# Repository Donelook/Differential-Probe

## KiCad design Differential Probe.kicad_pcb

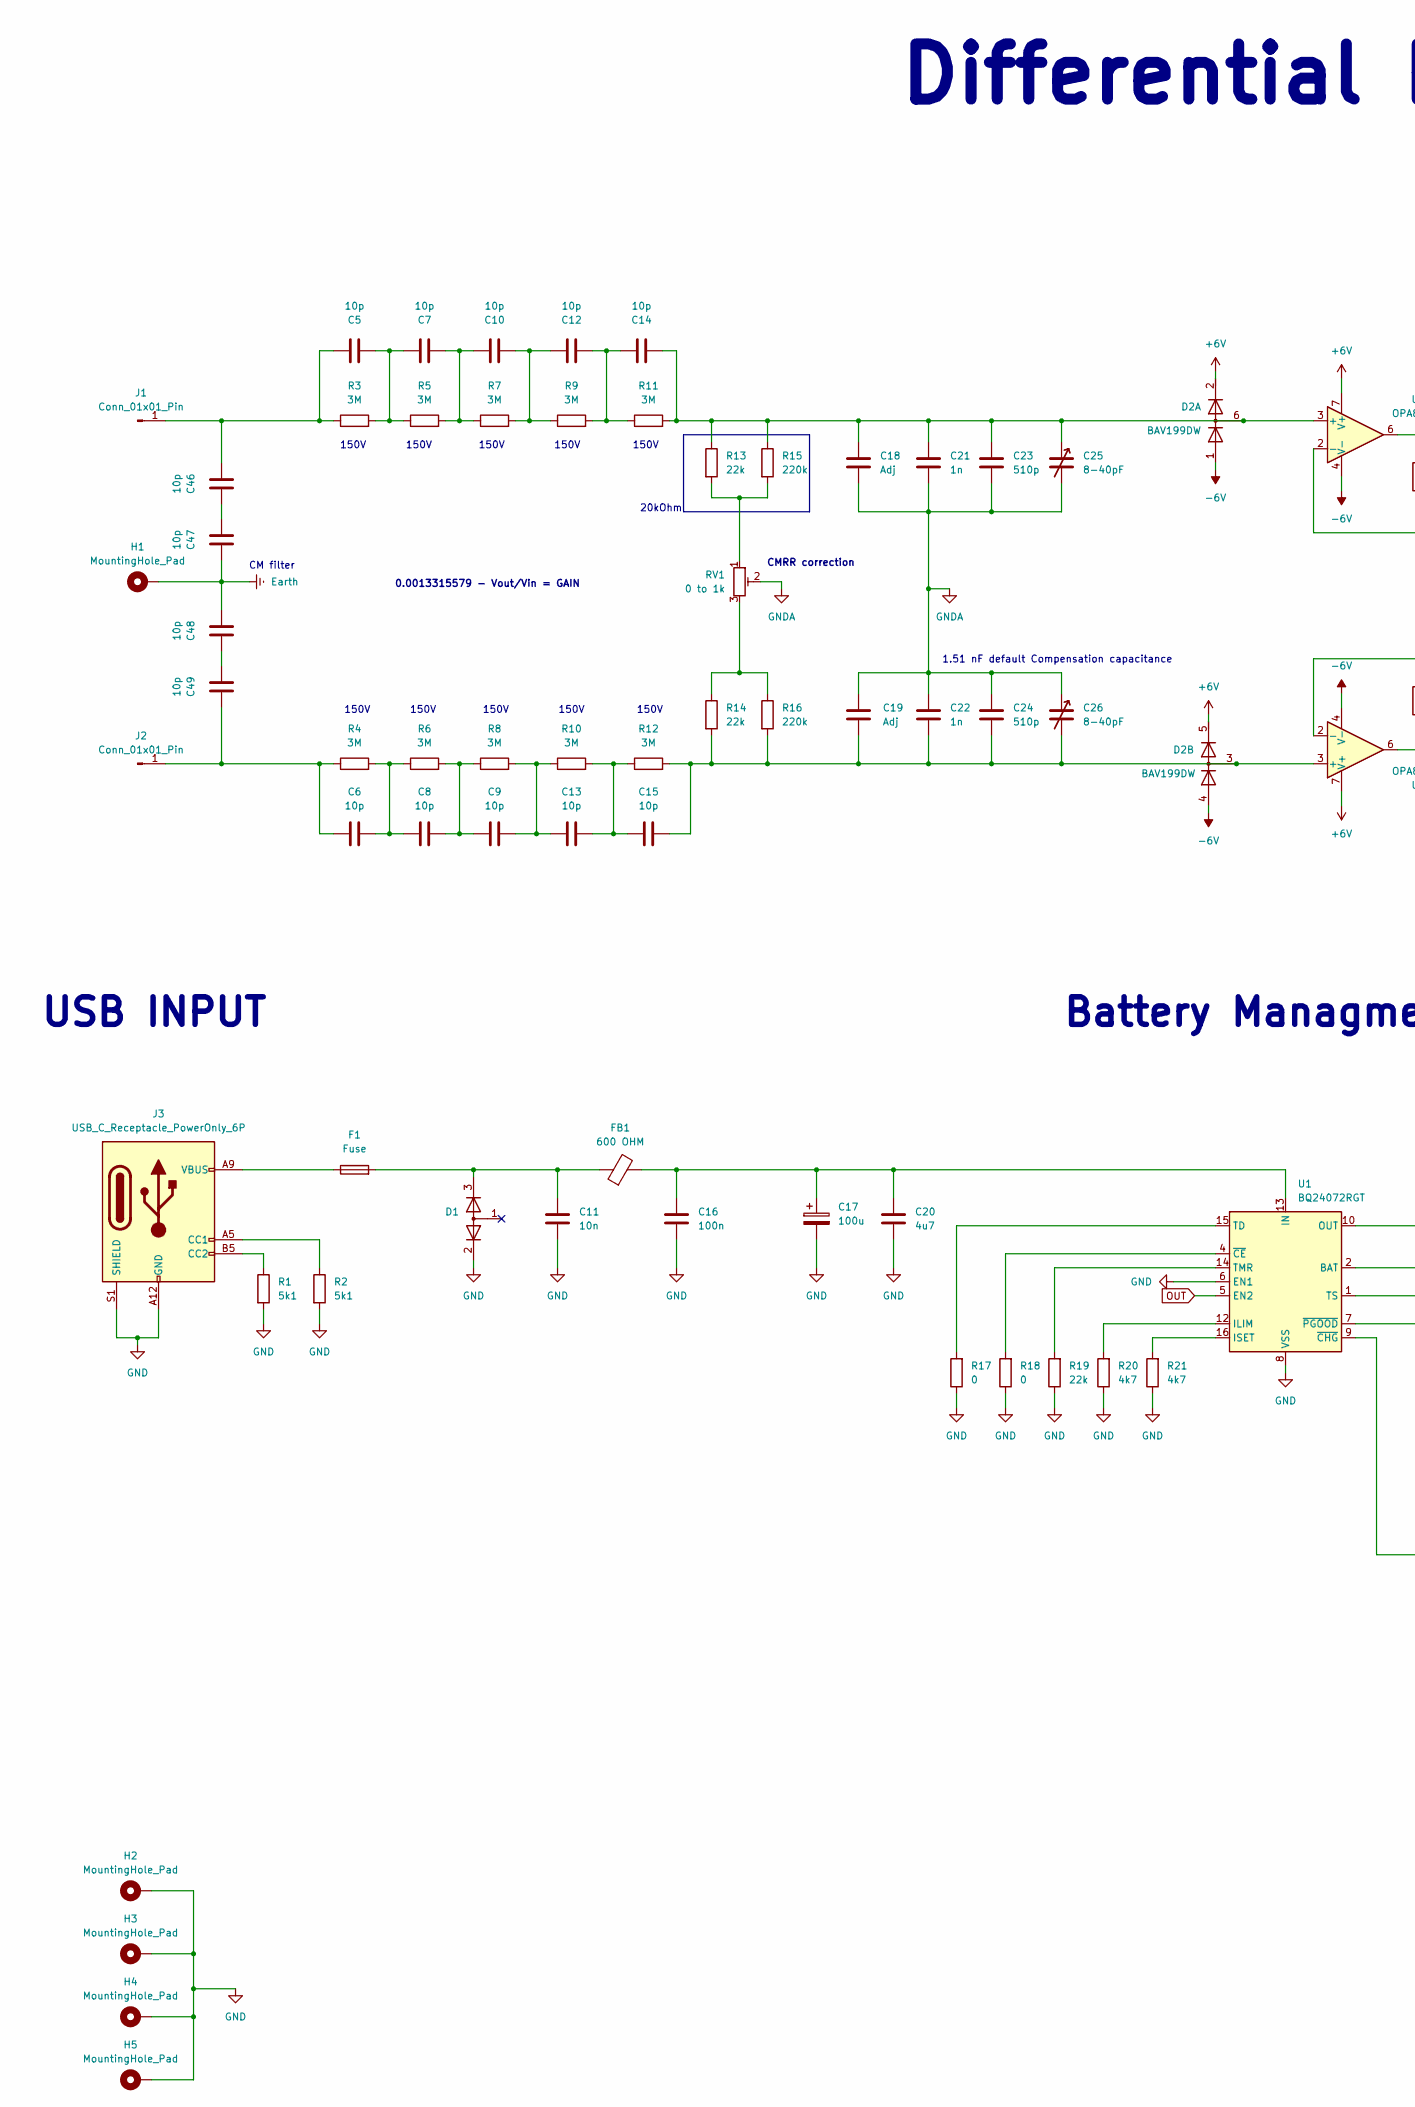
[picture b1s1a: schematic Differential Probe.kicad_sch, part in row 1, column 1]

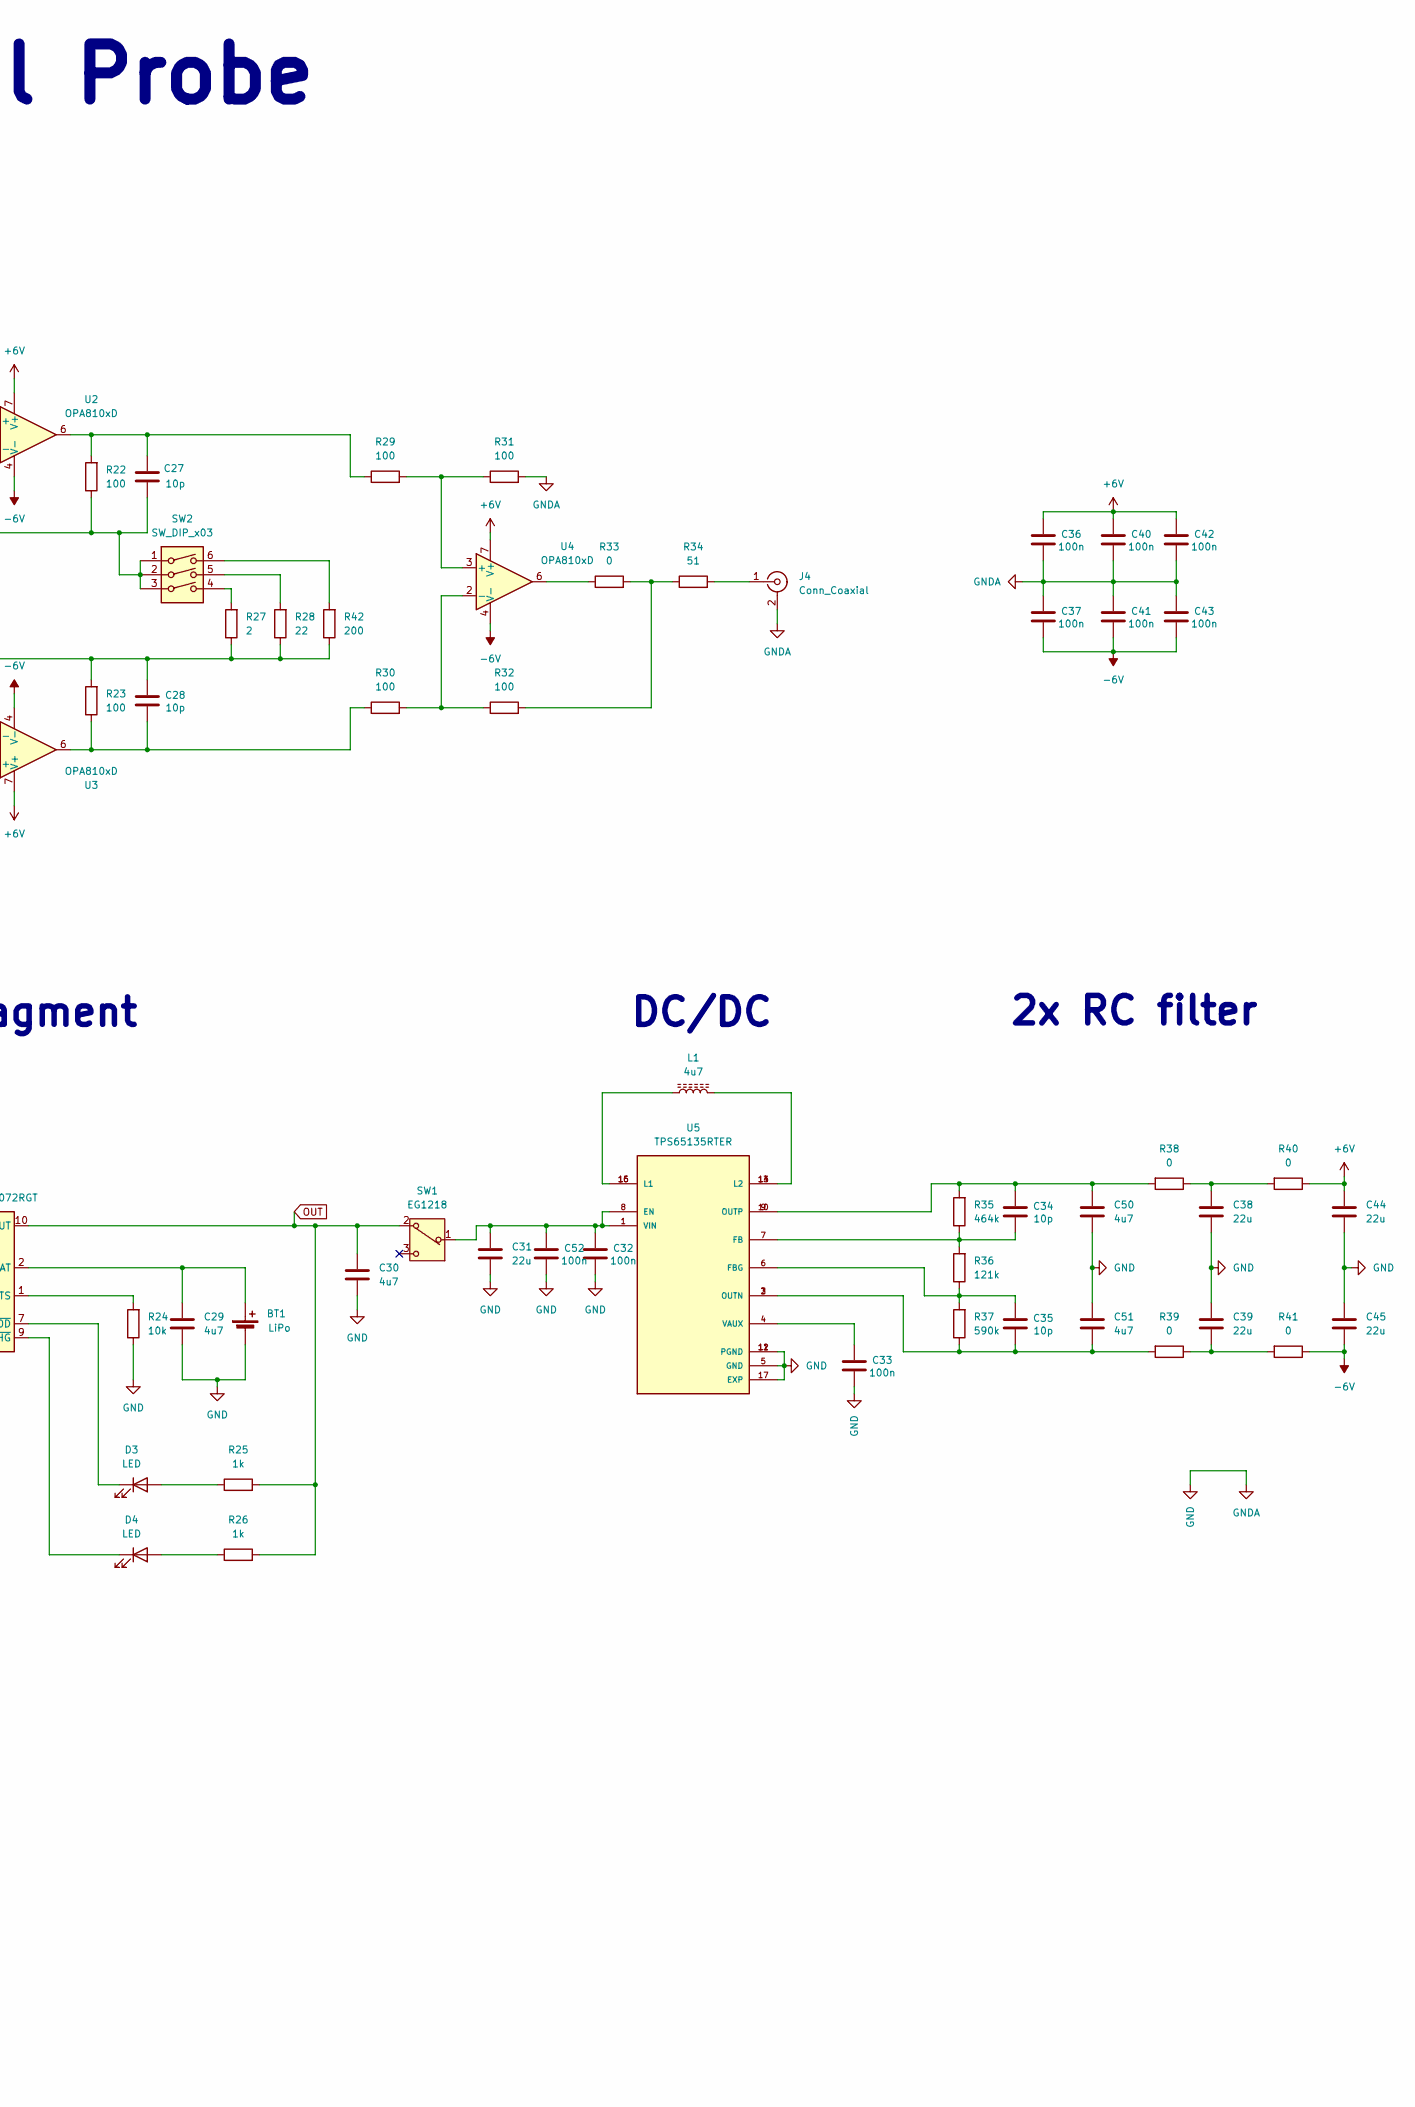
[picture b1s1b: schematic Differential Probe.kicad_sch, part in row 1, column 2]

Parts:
BT1: LiPo; PinHeader_1x02_P2.00mm_Vertical
C5, C6, C7, C8, C9, C10, C12, C13, C14, C15, C46, C47, C48, C49: 10p; C_1206_3216Metric_Pad1.33x1.80mm_HandSolder
C11: 10n; C_0603_1608Metric_Pad1.08x0.95mm_HandSolder
C16, C32, C33, C36, C37, C40, C41, C42, C43, C52: 100n; C_0603_1608Metric_Pad1.08x0.95mm_HandSolder
C17: 100u; CP_EIA-6032-28_Kemet-C_Pad2.25x2.35mm_HandSolder
C18, C19: Adj; C_0603_1608Metric_Pad1.08x0.95mm_HandSolder
C20, C29, C30, C50, C51: 4u7; C_0603_1608Metric_Pad1.08x0.95mm_HandSolder
C21, C22: 1n; C_0603_1608Metric_Pad1.08x0.95mm_HandSolder
C23, C24: 510p; C_0603_1608Metric_Pad1.08x0.95mm_HandSolder
C25, C26: 8-40pF; C_Trimmer_Voltronics_JZ
C27, C28, C34, C35: 10p; C_0603_1608Metric_Pad1.08x0.95mm_HandSolder
C31, C38, C39, C44, C45: 22u; C_1210_3225Metric
D1: D_Dual_CommonAnode_AKK; TSOT-23
D2: BAV199DW; SOT-363_SC-70-6
D3, D4: LED; D_0603_1608Metric_Pad1.05x0.95mm_HandSolder
F1: Fuse; Fuse_1206_3216Metric_Pad1.42x1.75mm_HandSolder
FB1: 600 OHM; L_1206_3216Metric_Pad1.22x1.90mm_HandSolder
H1, H2, H3, H4, H5: MountingHole_Pad; MountingHole_3.2mm_M3_DIN965_Pad
J1, J2: Conn_01x01_Pin; NetTie-2_SMD_Pad2.0mm
J3: USB_C_Receptacle_PowerOnly_6P; USB_C_Receptacle_GCT_USB4125-xx-x-0190_6P_TopMnt_Horizontal
J4: Conn_Coaxial; BNC_Molex_73100-0154-50_Horizontal
L1: 4u7; L_1008_2520Metric_Pad1.43x2.20mm_HandSolder
R1, R2: 5k1; R_0603_1608Metric_Pad0.98x0.95mm_HandSolder
R3, R4, R5, R6, R7, R8, R9, R10, R11, R12: 3M; R_1206_3216Metric_Pad1.30x1.75mm_HandSolder
R13, R14: 22k; R_0805_2012Metric_Pad1.20x1.40mm_HandSolder
R15, R16: 220k; R_0805_2012Metric_Pad1.20x1.40mm_HandSolder
R17, R18, R38, R39, R40, R41: 0; R_0603_1608Metric_Pad0.98x0.95mm_HandSolder
R19: 22k; R_0603_1608Metric_Pad0.98x0.95mm_HandSolder
R20, R21: 4k7; R_0603_1608Metric_Pad0.98x0.95mm_HandSolder
R22, R23, R29, R30, R31, R32: 100; R_0603_1608Metric_Pad0.98x0.95mm_HandSolder
R24: 10k; R_0603_1608Metric_Pad0.98x0.95mm_HandSolder
R25, R26: 1k; R_0603_1608Metric_Pad0.98x0.95mm_HandSolder
R27: 2; R_0603_1608Metric_Pad0.98x0.95mm_HandSolder
R28: 22; R_0603_1608Metric_Pad0.98x0.95mm_HandSolder
R33: 0; R_1206_3216Metric_Pad1.30x1.75mm_HandSolder
R34: 51; R_1206_3216Metric_Pad1.30x1.75mm_HandSolder
R35: 464k; R_0603_1608Metric_Pad0.98x0.95mm_HandSolder
R36: 121k; R_0603_1608Metric_Pad0.98x0.95mm_HandSolder
R37: 590k; R_0603_1608Metric_Pad0.98x0.95mm_HandSolder
R42: 200; R_0603_1608Metric_Pad0.98x0.95mm_HandSolder
RV1: 0 to 1k; Potentiometer_Bourns_3266W_Vertical
SW1: EG1218; SW_Slide-03_Wuerth-WS-SLTV_10x2.5x6.4_P2.54mm
SW2: SW_DIP_x03; SW_DIP_SPSTx03_Slide_KingTek_DSHP03TS_W7.62mm_P1.27mm
U1: BQ24072RGT; VQFN-16-1EP_3x3mm_P0.5mm_EP1.6x1.6mm
U2, U3, U4: OPA810xD; SOIC-8_3.9x4.9mm_P1.27mm
U5: TPS65135RTER; QFN50P300X300X80-17N; PARTREV January 2017

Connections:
+6V: C36.1, C40.1, C42.1, C44.1, D2.2 (K2), D2.5 (K4), R40.1, U2.7 (V+), U3.7 (V+), U4.7 (V+)
-6V: C37.2, C41.2, C43.2, C45.2, D2.1 (A1), D2.4 (A3), R41.1, U2.4 (V-), U3.4 (V-), U4.4 (V-)
Earth: C47.2, C48.1, H1.1
GND: BT1.2 (-), C11.2, C16.2, C17.2, C18.2, C19.1, C20.2, C21.2, C22.1, C23.2, C24.1, C25.2, C26.1, C29.2, C30.2, C31.2, C32.2, C33.2, C36.2, C37.1, C38.2, C39.1, C40.2, C41.1, C42.2, C43.1, C44.2, C45.1, C50.2, C51.1, C52.2, D1.2 (K), H2.1, H3.1, H4.1, H5.1, J3.A12 (GND), J3.B12 (GND), J3.S1 (SHIELD), J4.2 (Ext), R1.2, R2.2, R17.1, R18.1, R19.1, R20.1, R21.1, R24.1, R31.2, RV1.2, U1.6 (EN1), U1.8 (VSS), U1.17 (VSS), U5.5 (GND), U5.11 (PGND), U5.12 (PGND), U5.17 (EXP)
unnamed: BT1.1 (+), C29.1, U1.2 (BAT), U1.3 (BAT)
unnamed: C5.1, C7.2, R3.2, R5.1
unnamed: C6.2, C8.1, R4.2, R6.1
unnamed: C8.2, C9.1, R6.2, R8.1
unnamed: C10.1, C12.2, R7.2, R9.1
unnamed: C7.1, C10.2, R5.2, R7.1
unnamed: C11.1, D1.3 (K), F1.2, FB1.1
unnamed: C12.1, C14.2, R9.2, R11.1
unnamed: C9.2, C13.1, R8.2, R10.1
unnamed: C13.2, C15.1, R10.2, R12.1
unnamed: C27.1, R22.2, R29.1, U2.6
unnamed: C28.2, R23.1, R30.1, U3.6
unnamed: C34.1, C50.1, R35.2, R38.2, U5.9 (OUTP), U5.10 (OUTP)
unnamed: C35.2, C51.2, R37.1, R39.2, U5.2 (OUTN), U5.3 (OUTN)
unnamed: C38.1, R38.1, R40.2
unnamed: C39.2, R39.1, R41.2
unnamed: C46.2, C47.1
unnamed: C48.2, C49.1
unnamed: C14.1, C18.1, C21.1, C23.1, C25.1, D2.6 (K3A4), R11.2, R13.1, R15.1, U2.3 (+)
unnamed: C15.2, C19.2, C22.2, C24.2, C26.2, D2.3 (K1A2), R12.2, R14.2, R16.2, U3.3 (+)
unnamed: D3.2 (A), R25.1
unnamed: D3.1 (K), U1.7 (~PGOOD)
unnamed: D4.2 (A), R26.1
unnamed: D4.1 (K), U1.9 (~CHG)
unnamed: F1.1, J3.A9 (VBUS), J3.B9 (VBUS)
unnamed: C5.2, C46.1, J1.1, R3.1
unnamed: C6.1, C49.2, J2.1, R4.1
unnamed: J3.A5 (CC1), R2.1
unnamed: J3.B5 (CC2), R1.1
unnamed: J4.1 (In), R34.2
unnamed: L1.1, U5.15 (L1), U5.16 (L1)
unnamed: L1.2, U5.13 (L2), U5.14 (L2)
unnamed: R13.2, R15.2, RV1.1
unnamed: R14.1, R16.1, RV1.3
unnamed: R27.2, SW2.4
unnamed: R28.2, SW2.5
unnamed: R32.2, R33.2, R34.1
unnamed: R33.1, U4.6
unnamed: R42.2, SW2.6
unnamed: C31.1, C32.1, C52.1, SW1.1 (B), U5.1 (VIN), U5.8 (EN)
unnamed: R20.2, U1.12 (ILIM)
unnamed: C16.1, C17.1, C20.1, FB1.2, U1.13 (IN)
unnamed: R21.2, U1.16 (ISET)
unnamed: R17.2, U1.15 (TD)
unnamed: R19.2, U1.14 (TMR)
unnamed: R24.2, U1.1 (TS)
unnamed: R18.2, U1.4 (~CE)
unnamed: C27.2, R22.1, SW2.1, SW2.2, SW2.3, U2.2 (-)
unnamed: C28.1, R23.2, R27.1, R28.1, R42.1, U3.2 (-)
unnamed: R29.2, R31.1, U4.3 (+)
unnamed: R30.2, R32.1, U4.2 (-)
unnamed: C34.2, R35.1, R36.2, U5.7 (FB)
unnamed: C35.1, R36.1, R37.2, U5.6 (FBG)
unnamed: C33.1, U5.4 (VAUX)
OUT: C30.1, R25.2, R26.2, SW1.2 (C), U1.5 (EN2), U1.10 (OUT), U1.11 (OUT)

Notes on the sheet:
1.51 nF default Compensation capacitance
20kOhm
CM filter
150V
USB INPUT
CMRR correction
Differential Probe
2x RC filter
0.0013315579 - Vout/Vin = GAIN
Battery Managment
DC/DC

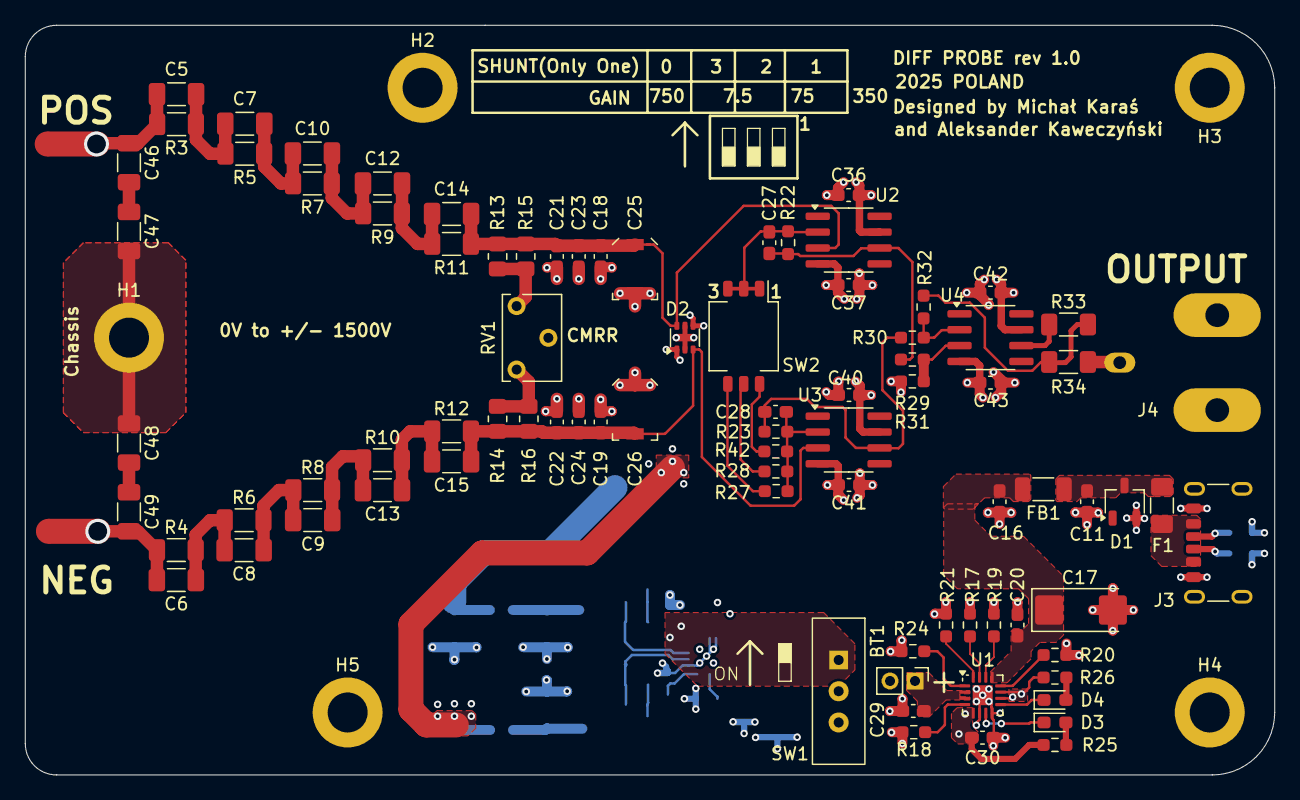
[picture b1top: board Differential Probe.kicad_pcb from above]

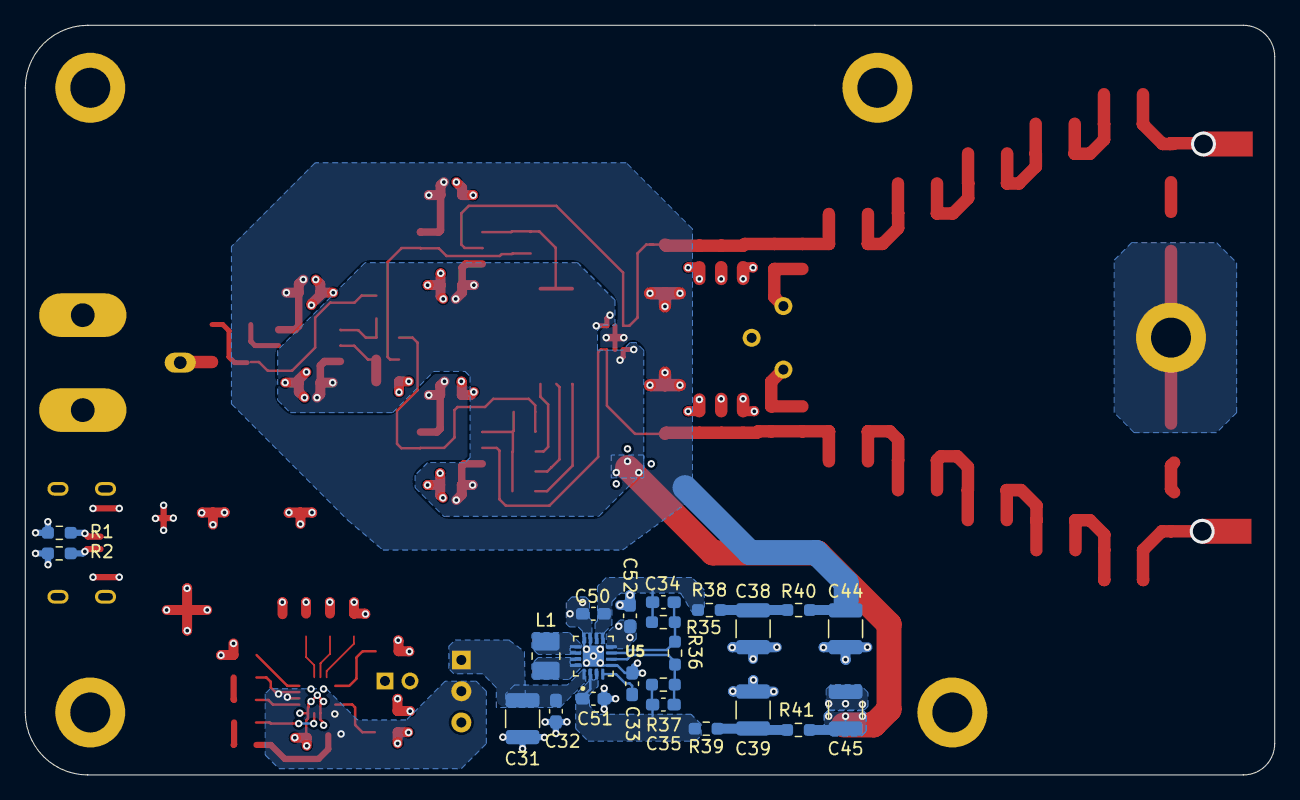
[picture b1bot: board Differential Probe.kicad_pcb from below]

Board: 4 copper layers, 100.0 x 60.0 mm, 115 parts (23 on the bottom side), 59 nets.

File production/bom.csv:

Designator,Footprint,Quantity,Value,LCSC Part #
BT1,PinHeader_1x02_P2.00mm_Vertical,1,LiPo,
"C10, C12, C13, C14, C15, C46, C47, C48, C49, C5, C6, C7, C8, C9",1206,14,10p,
C11,0603,1,10n,
"C16, C32, C33, C36, C37, C40, C41, C42, C43, C52",0603,10,100n,
C17,CP_EIA-6032-28_Kemet-C_Pad2.25x2.35mm_HandSolder,1,100u,
"C18, C19",0603,2,Adj,
"C20, C29, C30, C50, C51",0603,5,4u7,
"C21, C22",0603,2,1n,
"C23, C24",0603,2,510p,
"C25, C26",C_Trimmer_Voltronics_JZ,2,8-40pF,
"C27, C28, C34, C35",0603,4,10p,
"C31, C38, C39, C44, C45",1210,5,22u,
D1,TSOT-23,1,D_Dual_CommonAnode_AKK,
D2,SOT-363_SC-70-6,1,BAV199DW,
"D3, D4",0603,2,LED,
F1,1206,1,Fuse,
FB1,1206,1,600 OHM,
"J1, J2",NetTie-2_SMD_Pad2.0mm,2,Conn_01x01_Pin,
J3,USB_C_Receptacle_GCT_USB4125-xx-x-0190_6P_TopMnt_Horizontal,1,USB_C_Receptacle_PowerOnly_6P,
J4,BNC_Molex_73100-0154-50_Horizontal,1,Conn_Coaxial,
L1,1008,1,4u7,
"R1, R2",0603,2,5k1,
"R10, R11, R12, R3, R4, R5, R6, R7, R8, R9",1206,10,3M,
"R13, R14",0805,2,22k,
"R15, R16",0805,2,220k,
"R17, R18, R38, R39, R40, R41",0603,6,0,
R19,0603,1,22k,
"R20, R21",0603,2,4k7,
"R22, R23, R29, R30, R31, R32",0603,6,100,
R24,0603,1,10k,
"R25, R26",0603,2,1k,
R27,0603,1,2,
R28,0603,1,22,
R33,1206,1,0,
R34,1206,1,51,
R35,0603,1,464k,
R36,0603,1,121k,
R37,0603,1,590k,
R42,0603,1,200,
RV1,Potentiometer_Bourns_3266W_Vertical,1,0 to 1k,
SW1,SW_Slide-03_Wuerth-WS-SLTV_10x2.5x6.4_P2.54mm,1,EG1218,
SW2,SW_DIP_SPSTx03_Slide_KingTek_DSHP03TS_W7.62mm_P1.27mm,1,SW_DIP_x03,
U1,VQFN-16-1EP_3x3mm_P0.5mm_EP1.6x1.6mm,1,BQ24072RGT,
"U2, U3, U4",SOIC-8_3.9x4.9mm_P1.27mm,3,OPA810xD,
U5,QFN50P300X300X80-17N,1,TPS65135RTER,

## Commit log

2025-03-23 first push
2025-03-23 Next work push
    added callculator for instrumental ampl
2025-03-24 battery circuit added
2025-03-25 Layout started
2025-03-28 PCB layout 90%
2025-03-29 Ready to check
2025-03-29 3D model added
    BNC
2025-03-30 Done
